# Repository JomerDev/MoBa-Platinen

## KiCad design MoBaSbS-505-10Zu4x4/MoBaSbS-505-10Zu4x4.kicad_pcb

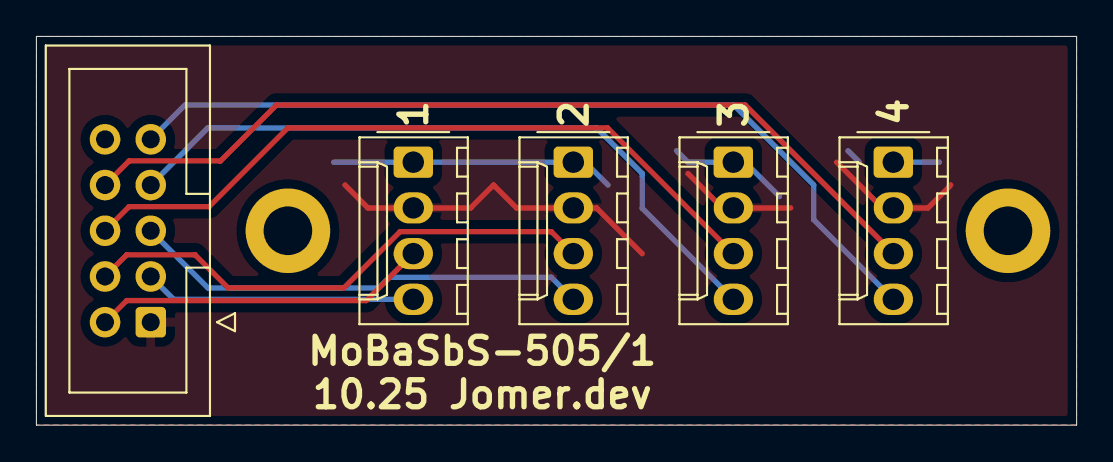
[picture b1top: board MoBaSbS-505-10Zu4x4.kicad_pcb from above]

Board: 2 copper layers, 57.8 x 21.6 mm, 7 parts (0 on the bottom side), 10 nets.

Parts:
H1, H3: MountingHole_Pad; MountingHole_2.7mm_M2.5_DIN965_Pad
J1: Conn_02x05_Odd_Even; IDC-Header_2x05_P2.54mm_Vertical
J10: 1; Molex_KK-254_AE-6410-04A_1x04_P2.54mm_Vertical
J11: 2; Molex_KK-254_AE-6410-04A_1x04_P2.54mm_Vertical
J12: 3; Molex_KK-254_AE-6410-04A_1x04_P2.54mm_Vertical
J13: 4; Molex_KK-254_AE-6410-04A_1x04_P2.54mm_Vertical

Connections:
/GND: J1.1, J10.2, J11.2, J12.2, J13.2
/PIN_1: J1.2, J10.3
/PIN_2: J1.3, J10.4
/PIN_3: J1.4, J11.3
/PIN_4: J1.5, J11.4
/PIN_5: J1.6, J12.3
/PIN_6: J1.7, J12.4
/PIN_7: J1.8, J13.3
/PIN_8: J1.9, J13.4
/POWER: J1.10, J10.1, J11.1, J12.1, J13.1

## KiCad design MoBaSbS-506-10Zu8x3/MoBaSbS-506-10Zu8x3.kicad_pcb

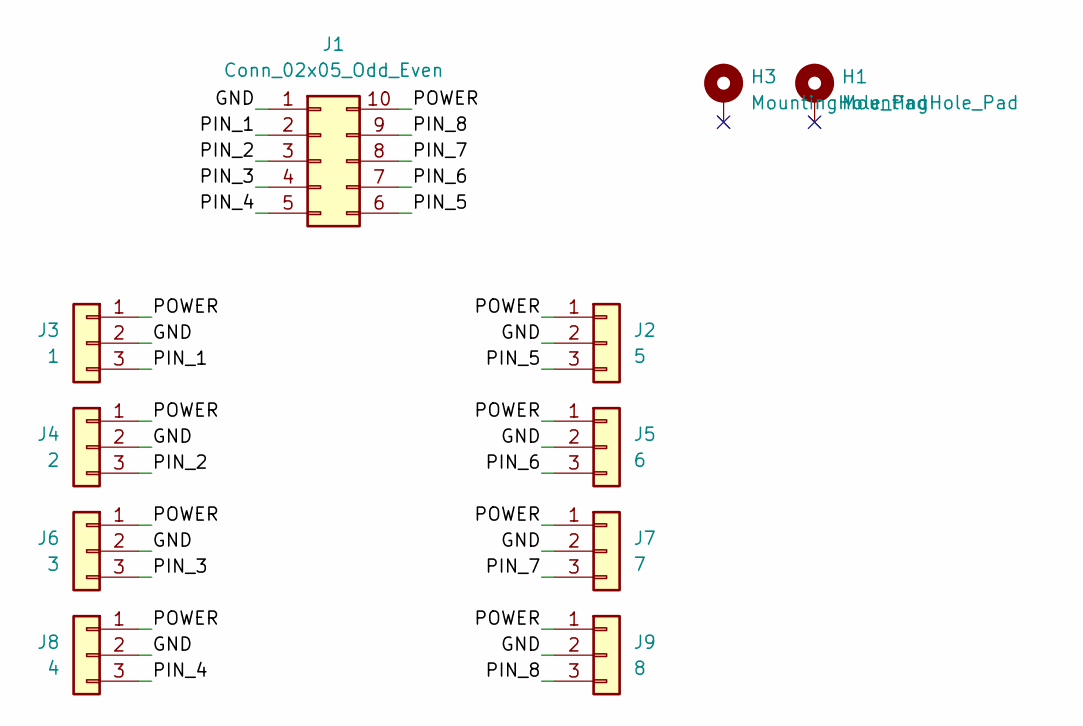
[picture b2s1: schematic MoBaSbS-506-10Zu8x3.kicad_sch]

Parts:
H1, H3: MountingHole_Pad; MountingHole_2.7mm_M2.5_DIN965_Pad
J1: Conn_02x05_Odd_Even; IDC-Header_2x05_P2.54mm_Vertical
J2: 5; Molex_KK-254_AE-6410-03A_1x03_P2.54mm_Vertical
J3: 1; Molex_KK-254_AE-6410-03A_1x03_P2.54mm_Vertical
J4: 2; Molex_KK-254_AE-6410-03A_1x03_P2.54mm_Vertical
J5: 6; Molex_KK-254_AE-6410-03A_1x03_P2.54mm_Vertical
J6: 3; Molex_KK-254_AE-6410-03A_1x03_P2.54mm_Vertical
J7: 7; Molex_KK-254_AE-6410-03A_1x03_P2.54mm_Vertical
J8: 4; Molex_KK-254_AE-6410-03A_1x03_P2.54mm_Vertical
J9: 8; Molex_KK-254_AE-6410-03A_1x03_P2.54mm_Vertical

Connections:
/GND: J1.1, J2.2, J3.2, J4.2, J5.2, J6.2, J7.2, J8.2, J9.2
/PIN_1: J1.2, J3.3
/PIN_2: J1.3, J4.3
/PIN_3: J1.4, J6.3
/PIN_4: J1.5, J8.3
/PIN_5: J1.6, J2.3
/PIN_6: J1.7, J5.3
/PIN_7: J1.8, J7.3
/PIN_8: J1.9, J9.3
/POWER: J1.10, J2.1, J3.1, J4.1, J5.1, J6.1, J7.1, J8.1, J9.1

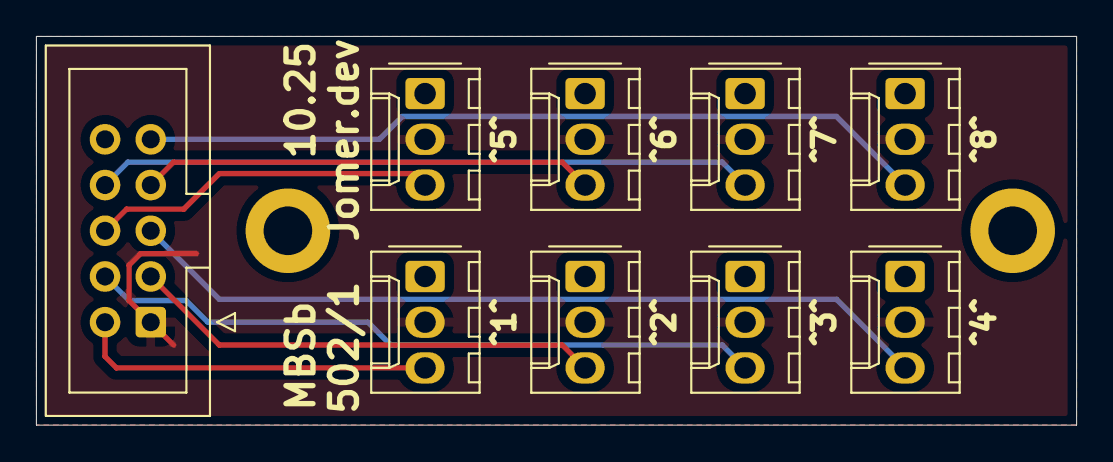
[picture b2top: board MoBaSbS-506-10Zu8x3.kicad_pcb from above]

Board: 2 copper layers, 57.8 x 21.6 mm, 11 parts (0 on the bottom side), 10 nets.

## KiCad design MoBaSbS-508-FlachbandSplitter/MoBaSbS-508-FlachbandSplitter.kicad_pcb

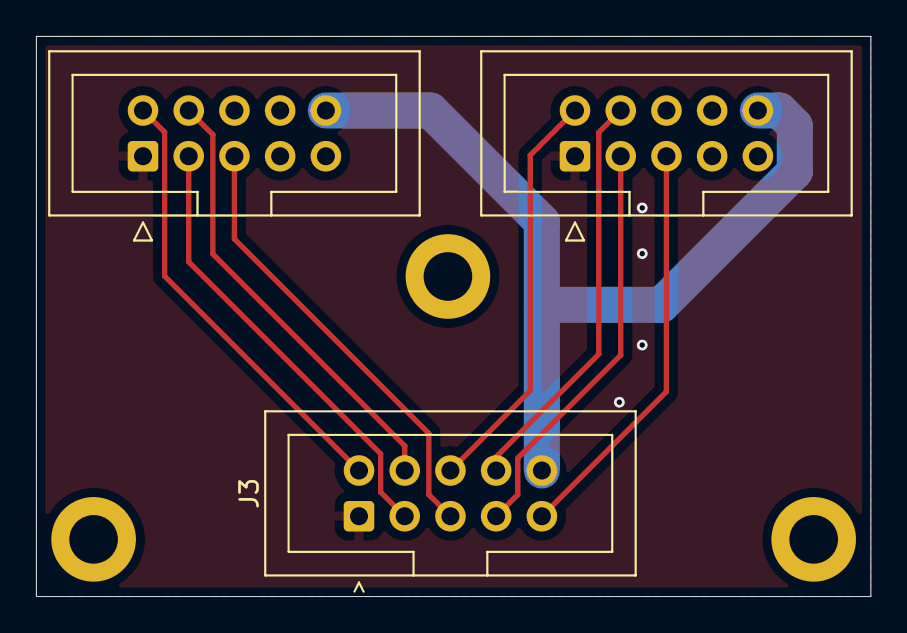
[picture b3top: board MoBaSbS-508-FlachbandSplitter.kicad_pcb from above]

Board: 2 copper layers, 46.4 x 31.1 mm, 6 parts (0 on the bottom side), 10 nets.

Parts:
H2, H3, H4: MountingHole_Pad; MountingHole_2.7mm_M2.5_DIN965_Pad
J2, J3: Conn_02x05_Counter_Clockwise; IDC-Header_2x05_P2.54mm_Vertical
Jw: Conn_02x05_Counter_Clockwise; IDC-Header_2x05_P2.54mm_Vertical

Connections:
/GND: J2.1, J3.1, Jw.1
/PIN_1: J3.2, Jw.2
/PIN_2: J3.3, Jw.3
/PIN_3: J3.4, Jw.4
/PIN_4: J3.5, Jw.5
/PIN_5: J2.2, J3.6
/PIN_6: J2.3, J3.7
/PIN_7: J2.4, J3.8
/PIN_8: J2.5, J3.9
/POWER: J2.10, J3.10, Jw.10
